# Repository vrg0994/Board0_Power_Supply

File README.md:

# Board 0: 5V to 3.3V Power Supply PCB

## 📝 Project Overview
This is my first custom Printed Circuit Board (PCB), designed entirely from scratch in **KiCad**. The purpose of this board is to take a standard 5V input and regulate it down to a stable 3.3V output, which will be used to power future microcontroller projects (including a custom STM32 Flight Controller).

## ⚙️ Technical Specifications
*   **Input Voltage:** 5V DC (via 2-pin header)
*   **Output Voltage:** 3.3V DC (via 2-pin header)
*   **Main Component:** LD1117S33TR (SOT-223 package) Low Dropout Regulator
*   **Indicators:** Power-on LED with 150Ω current-limiting resistor
*   **Board Layers:** 2-Layer (Top Copper + Bottom Copper)
*   **Dimensions:** 27mm x 45mm

## 📐 Design Files
*   **Source:** The `/Hardware` folder contains all KiCad source files.
*   **Manufacturing:** The `/Gerbers` folder contains the zipped files ready to be sent to a manufacturer.
*   **Design Check (DRC):** 0 Errors, 0 Unconnected Items.

## 🖼️ Design Preview

## 🛠️ Tools Used
*   **KiCad 10.0** (Schematic Capture & PCB Layout)

## 🚀 Future Plans
This board is step one of a larger project: **Designing a custom Flight Controller**. Next steps include integrating an STM32 Microcontroller, an IMU (Gyroscope/Accelerometer), and USB-C connectivity.

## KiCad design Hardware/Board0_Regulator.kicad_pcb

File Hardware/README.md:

This folder contains the KiCad source files for Board 0

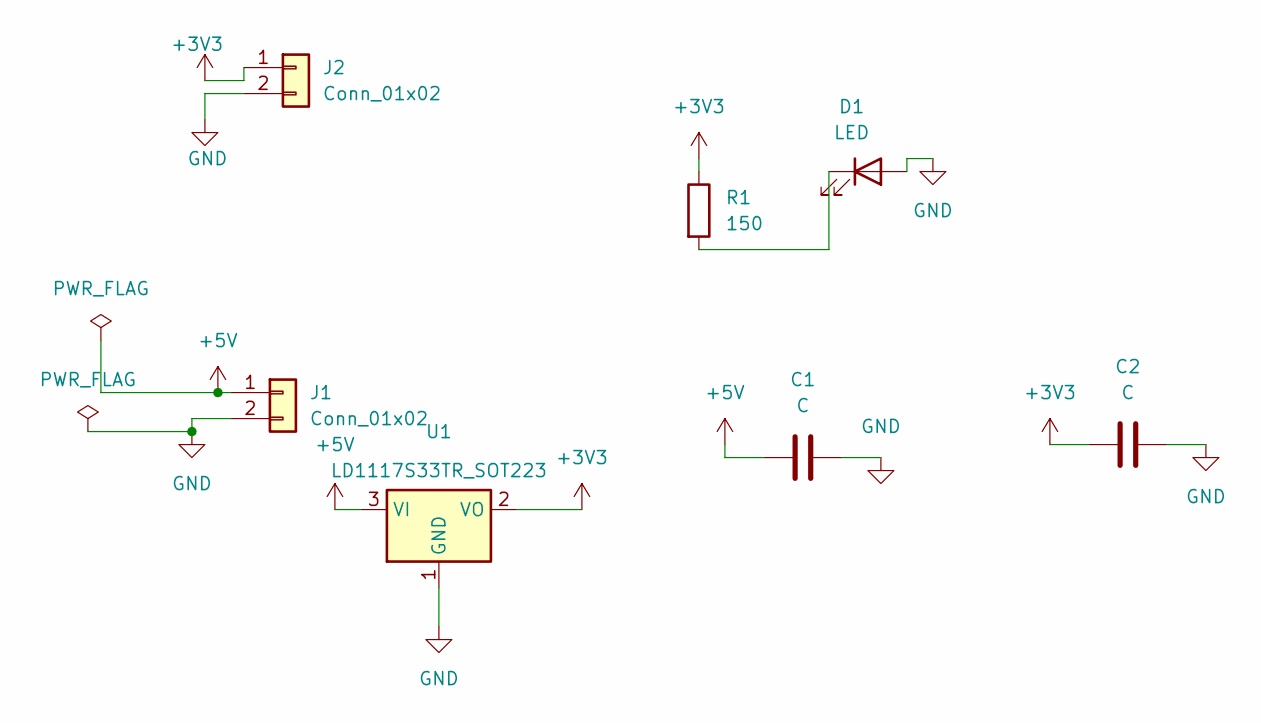
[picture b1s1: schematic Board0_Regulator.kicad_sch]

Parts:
C1, C2: C; C_0805_2012Metric
D1: LED; LED_0805_2012Metric
J1, J2: Conn_01x02; PinHeader_1x02_P2.54mm_Vertical
R1: 150; R_0805_2012Metric
U1: LD1117S33TR_SOT223; SOT-223-3_TabPin2

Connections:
+3V3: C2.1, J2.1, R1.1, U1.2 (VO)
+5V: C1.1, J1.1, U1.3 (VI)
GND: C1.2, C2.2, D1.2 (A), J1.2, J2.2, U1.1 (GND)
unnamed: D1.1 (K), R1.2

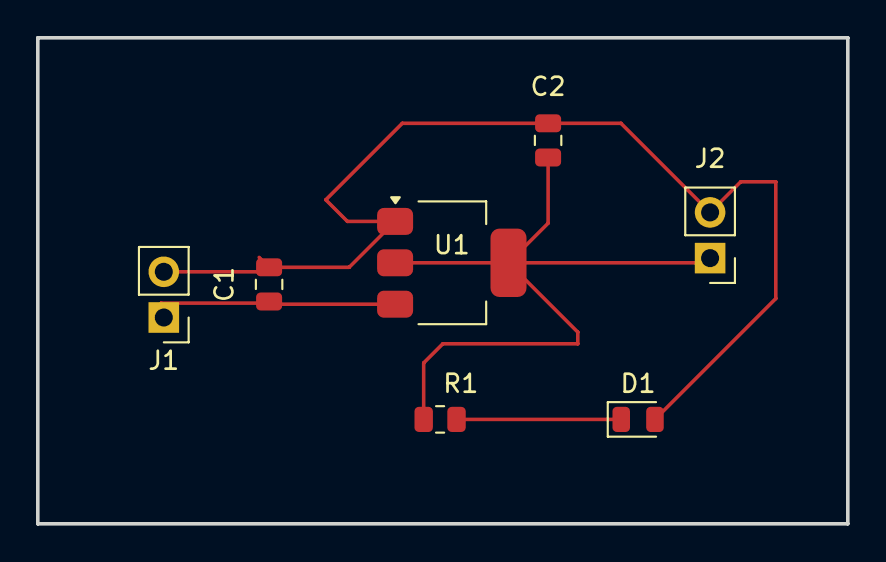
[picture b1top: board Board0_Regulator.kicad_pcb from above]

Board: 2 copper layers, 45.0 x 27.0 mm, 7 parts (0 on the bottom side), 4 nets.
